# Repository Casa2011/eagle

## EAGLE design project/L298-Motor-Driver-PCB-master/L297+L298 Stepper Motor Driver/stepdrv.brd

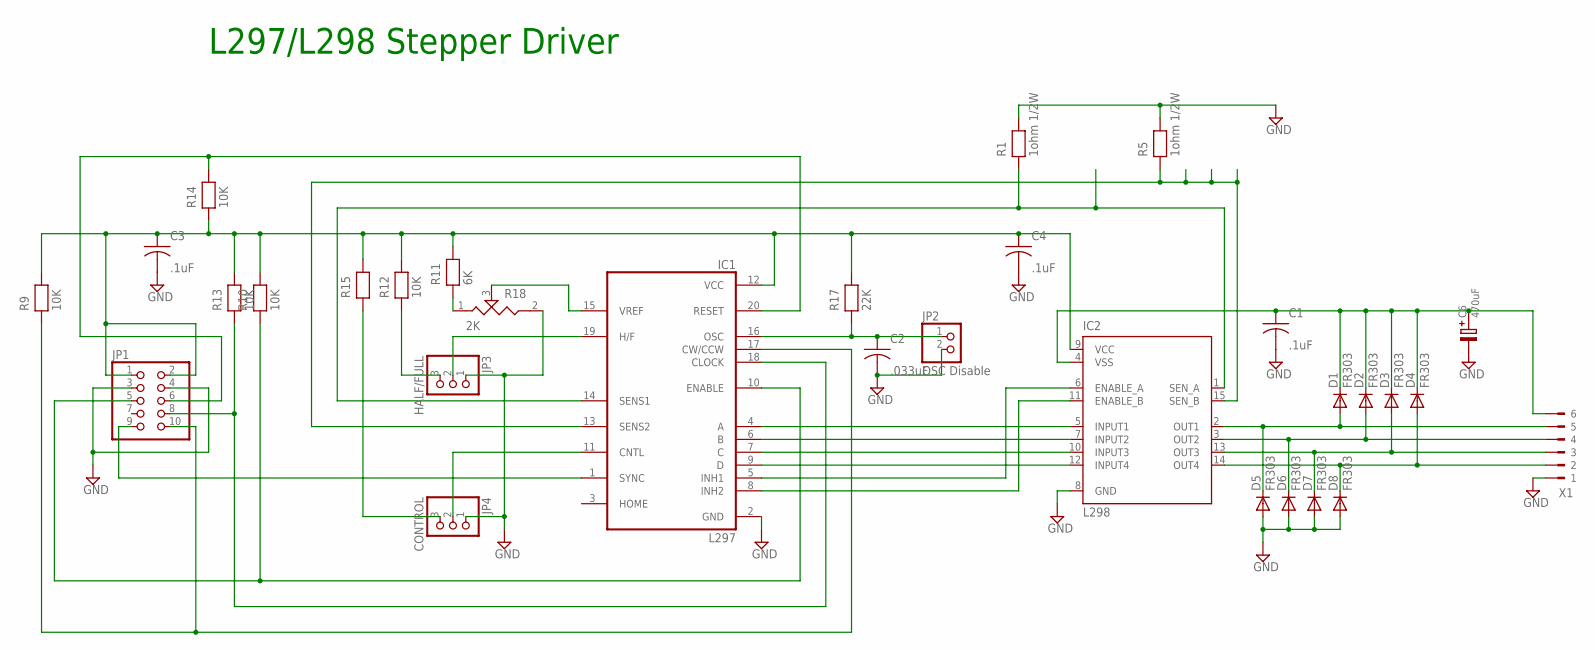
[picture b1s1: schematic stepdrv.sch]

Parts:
C1, C3, C4: .1uF; C-5
C2: .033uF; C-5
C6: 470uF; E5,0-12
D1, D2, D3, D4, D5, D6, D7, D8: FR303; DO201-15
IC1: L297; DIL20
IC2: L298; MULTIWATT-15
JP1: PINHD-2X5; 2X05
JP2: OSC Disable; 1X02
JP3: HALF/FULL; 1X03
JP4: CONTROL; 1X03
R1, R5: 1ohm 1/2W; R-12,5
R9, R10, R12, R13, R14: 10K; R-10
R11: 6K; R-10
R15: RESEU-10; R-10
R17: 22K; R-10
R18: 2K; PT-10S
X1: 90-6

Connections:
GND: C1.2, C2.2, C3.2, C4.2, C6.-, D5.A, D6.A, D7.A, D8.A, IC1.2 (GND), IC2.8 (GND), JP1.3, JP1.4, JP2.2, JP3.1, JP4.1, R1.2, R5.2, R18.2, X1.1
unnamed: D1.A, D5.C, IC2.2 (OUT1), X1.5
unnamed: IC1.4 (A), IC2.5 (INPUT1)
unnamed: IC1.6 (B), IC2.7 (INPUT2)
unnamed: IC1.7 (C), IC2.10 (INPUT3)
unnamed: IC1.9 (D), IC2.12 (INPUT4)
unnamed: IC1.14 (SENS1), IC2.1 (SEN_A), R1.1
unnamed: IC1.13 (SENS2), IC2.15 (SEN_B), R5.1
unnamed: IC1.1 (SYNC), JP1.9
unnamed: IC1.18 (CLOCK), JP1.8, R13.1
unnamed: IC1.17 (CW/CCW), JP1.10, R9.1
unnamed: C2.1, IC1.16 (OSC), JP2.1, R17.1
unnamed: IC1.20 (RESET), JP1.6, R14.2
unnamed: R11.1, R18.1
unnamed: IC1.19 (H/F), JP3.2
unnamed: IC1.11 (CNTL), JP4.2
unnamed: IC1.15 (VREF), R18.3
unnamed: JP3.3, R12.1
unnamed: D2.A, D6.C, IC2.3 (OUT2), X1.4
unnamed: IC1.5 (INH1), IC2.6 (ENABLE_A)
unnamed: IC1.8 (INH2), IC2.11 (ENABLE_B)
unnamed: D3.A, D7.C, IC2.13 (OUT3), X1.3
unnamed: D4.A, D8.C, IC2.14 (OUT4), X1.2
unnamed: IC1.10 (ENABLE), JP1.5, R10.1
unnamed: JP4.3, R15.1
VCC: C3.1, C4.1, IC1.12 (VCC), IC2.9 (VCC), JP1.1, JP1.2, R9.2, R10.2, R11.2, R12.2, R13.2, R14.1, R15.2, R17.2
VSS: C1.1, C6.+, D1.C, D2.C, D3.C, D4.C, IC2.4 (VSS), X1.6

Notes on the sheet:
L297/L298 Stepper Driver

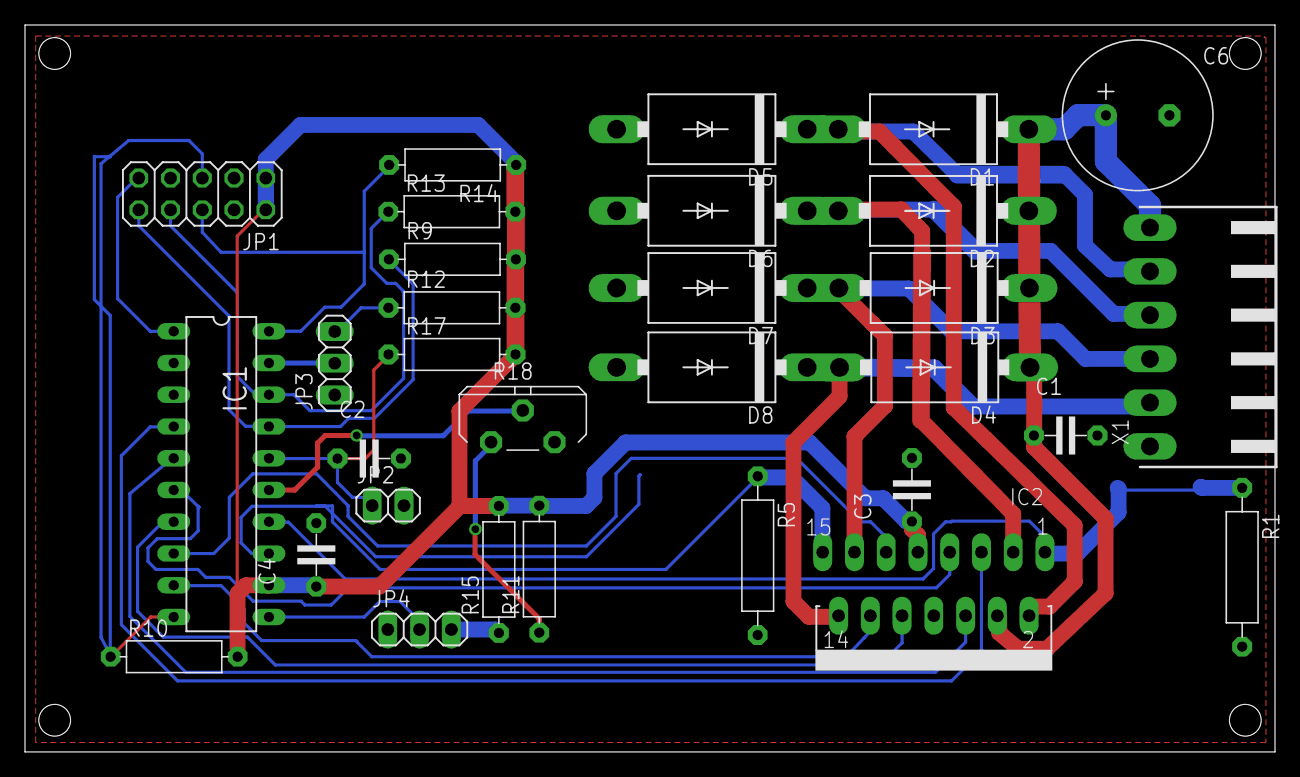
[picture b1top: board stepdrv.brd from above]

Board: 2 copper layers, 100.0 x 58.2 mm, 31 parts (0 on the bottom side), 27 nets.

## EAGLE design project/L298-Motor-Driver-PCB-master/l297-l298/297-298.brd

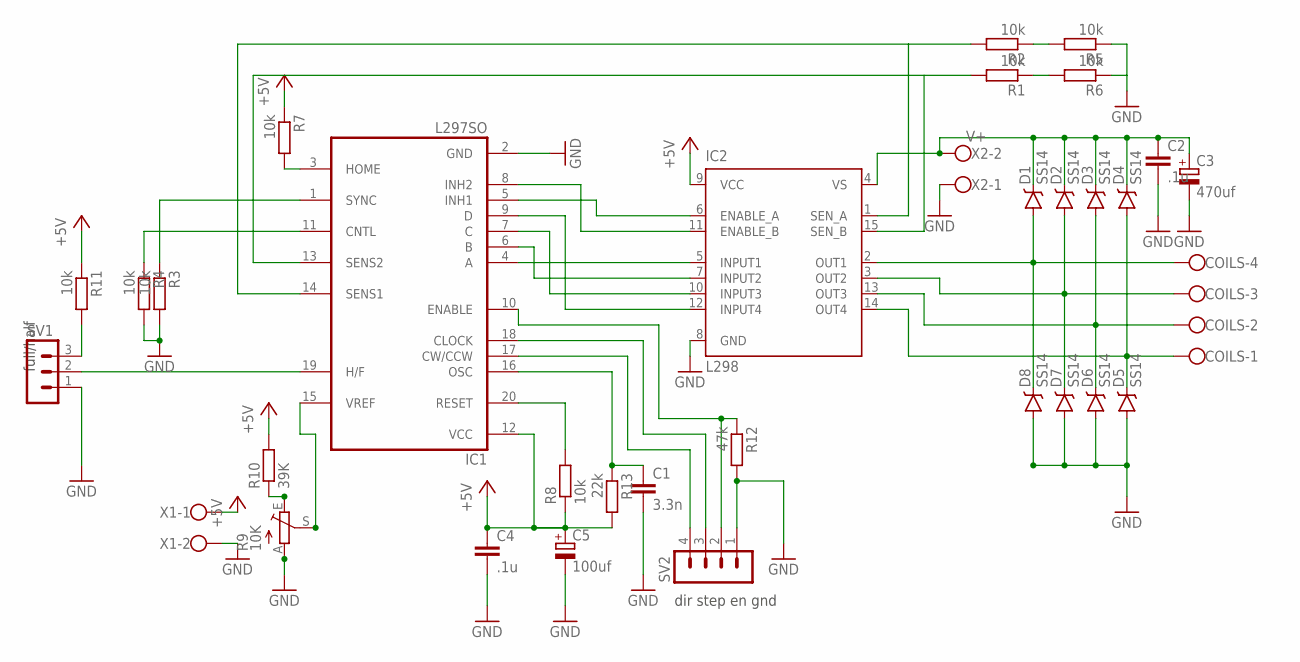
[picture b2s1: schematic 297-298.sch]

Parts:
C1: 3.3n; C0805
C2, C4: .1u; C0805
C3: 470uf; E3,5-8
C5: 100uf; E3,5-8
COILS: W237-4
D1, D2, D3, D4, D5, D6, D7, D8: SS14; SMA-DIODE
IC1: L297SO; SO20
IC2: L298; MULTIWATT-15
R1, R2, R5, R6: 10k; R2512
R3, R4, R7, R8, R11: 10k; R0805
R9: 10K; CA9V
R10: 39K; R0805
R12: 47k; R0805
R13: 22k; R0805
SV1: MA03-1
SV2: MA04-1
X1: W237-102
X2: V+; W237-102

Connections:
+5V: C4.1, C5.+, IC1.12 (VCC), IC2.9 (VCC), R7.1, R8.1, R10.2, R11.1, R13.2, X1.1
GND: C1.2, C2.2, C3.-, C4.2, C5.-, D5.A, D6.A, D7.A, D8.A, IC1.2 (GND), IC2.8 (GND), R3.2, R4.2, R5.P$1 (1), R6.P$1 (1), R9.A, R12.2, SV1.1, SV2.1, X1.2, X2.1
unnamed: IC1.4 (A), IC2.5 (INPUT1)
unnamed: IC1.6 (B), IC2.7 (INPUT2)
unnamed: IC1.7 (C), IC2.10 (INPUT3)
unnamed: IC1.9 (D), IC2.12 (INPUT4)
unnamed: IC1.8 (INH2), IC2.11 (ENABLE_B)
unnamed: IC1.5 (INH1), IC2.6 (ENABLE_A)
unnamed: IC1.15 (VREF), R9.S
unnamed: R9.E, R10.1
unnamed: COILS.4, D1.A, D8.C, IC2.2 (OUT1)
unnamed: COILS.3, D2.A, D7.C, IC2.3 (OUT2)
unnamed: COILS.2, D3.A, D6.C, IC2.13 (OUT3)
unnamed: COILS.1, D4.A, D5.C, IC2.14 (OUT4)
unnamed: IC1.13 (SENS2), IC2.15 (SEN_B), R1.P$2 (2)
unnamed: IC1.14 (SENS1), IC2.1 (SEN_A), R2.P$2 (2)
unnamed: IC1.1 (SYNC), R3.1
unnamed: IC1.19 (H/F), SV1.2
unnamed: R11.2, SV1.3
unnamed: IC1.10 (ENABLE), R12.1, SV2.2
unnamed: IC1.18 (CLOCK), SV2.3
unnamed: IC1.17 (CW/CCW), SV2.4
unnamed: C1.1, IC1.16 (OSC), R13.1
unnamed: IC1.11 (CNTL), R4.1
unnamed: IC1.3 (HOME), R7.2
unnamed: C2.1, C3.+, D1.C, D2.C, D3.C, D4.C, IC2.4 (VS), X2.2
unnamed: IC1.20 (RESET), R8.2
unnamed: R2.P$1 (1), R5.P$2 (2)
unnamed: R1.P$1 (1), R6.P$2 (2)

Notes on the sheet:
dir step en gnd
full/half

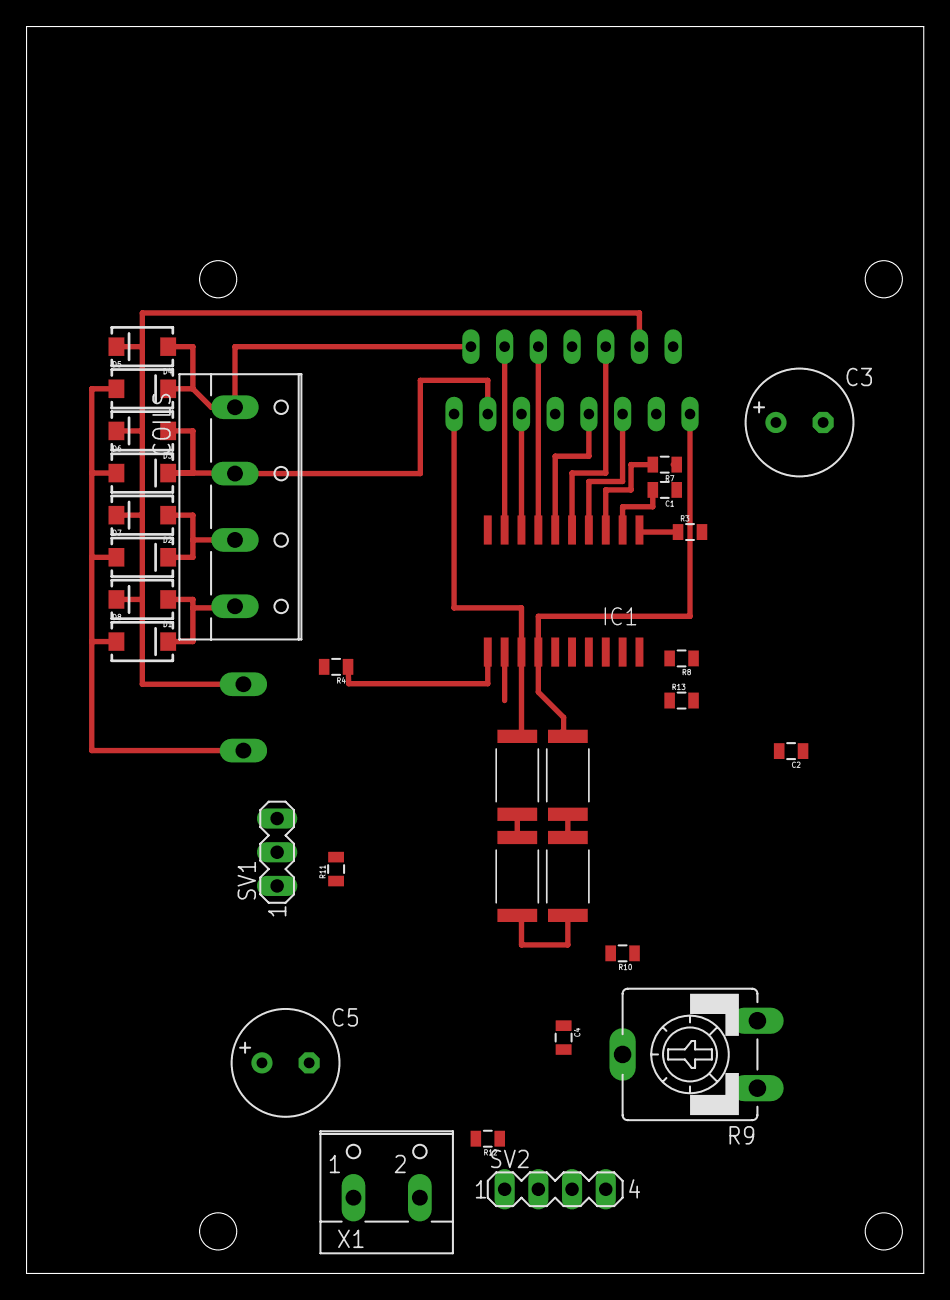
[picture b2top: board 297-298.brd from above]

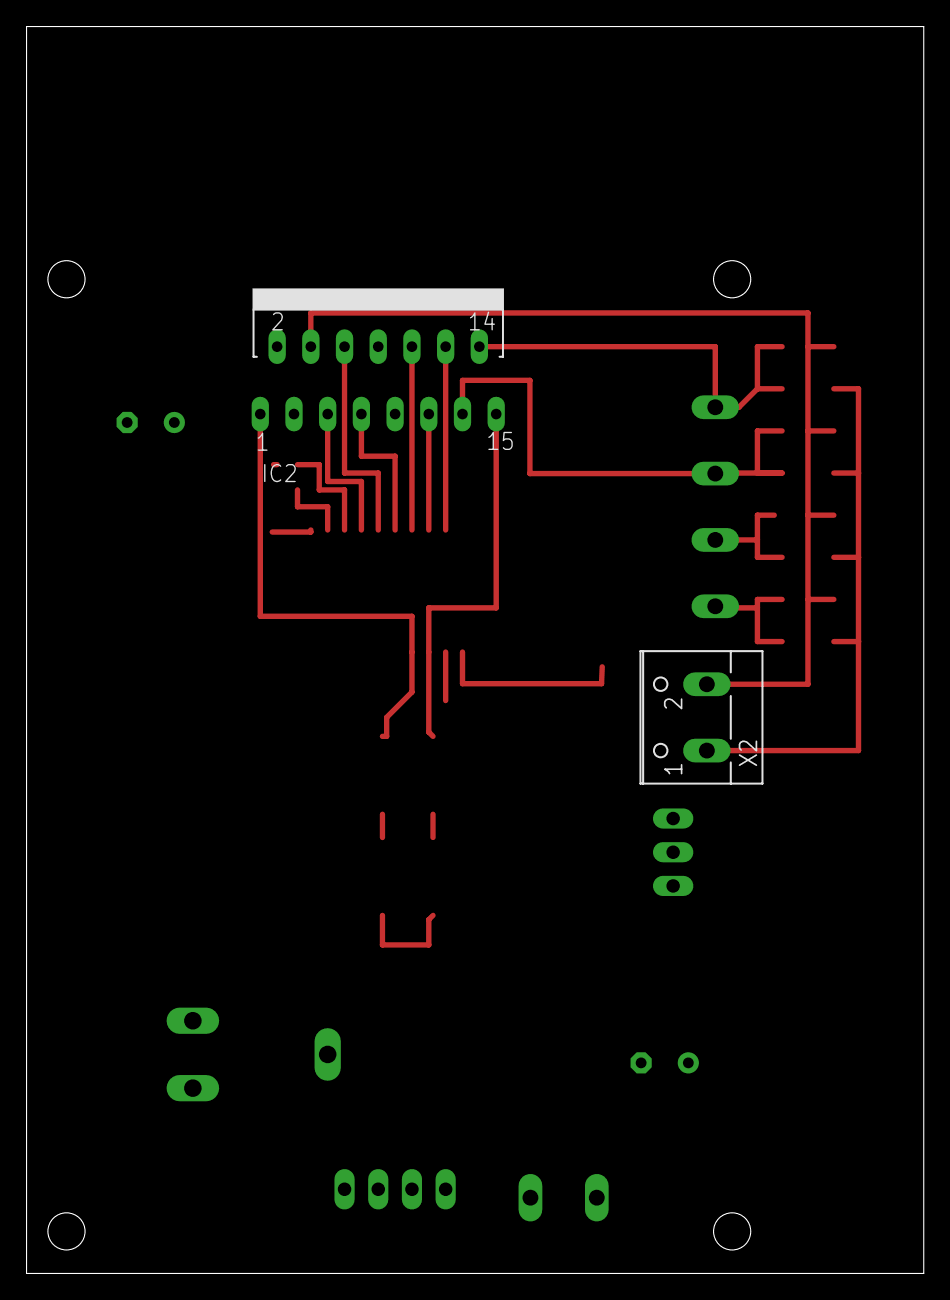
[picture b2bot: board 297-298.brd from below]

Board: 2 copper layers, 67.6 x 94.0 mm, 33 parts (2 on the bottom side), 29 nets.

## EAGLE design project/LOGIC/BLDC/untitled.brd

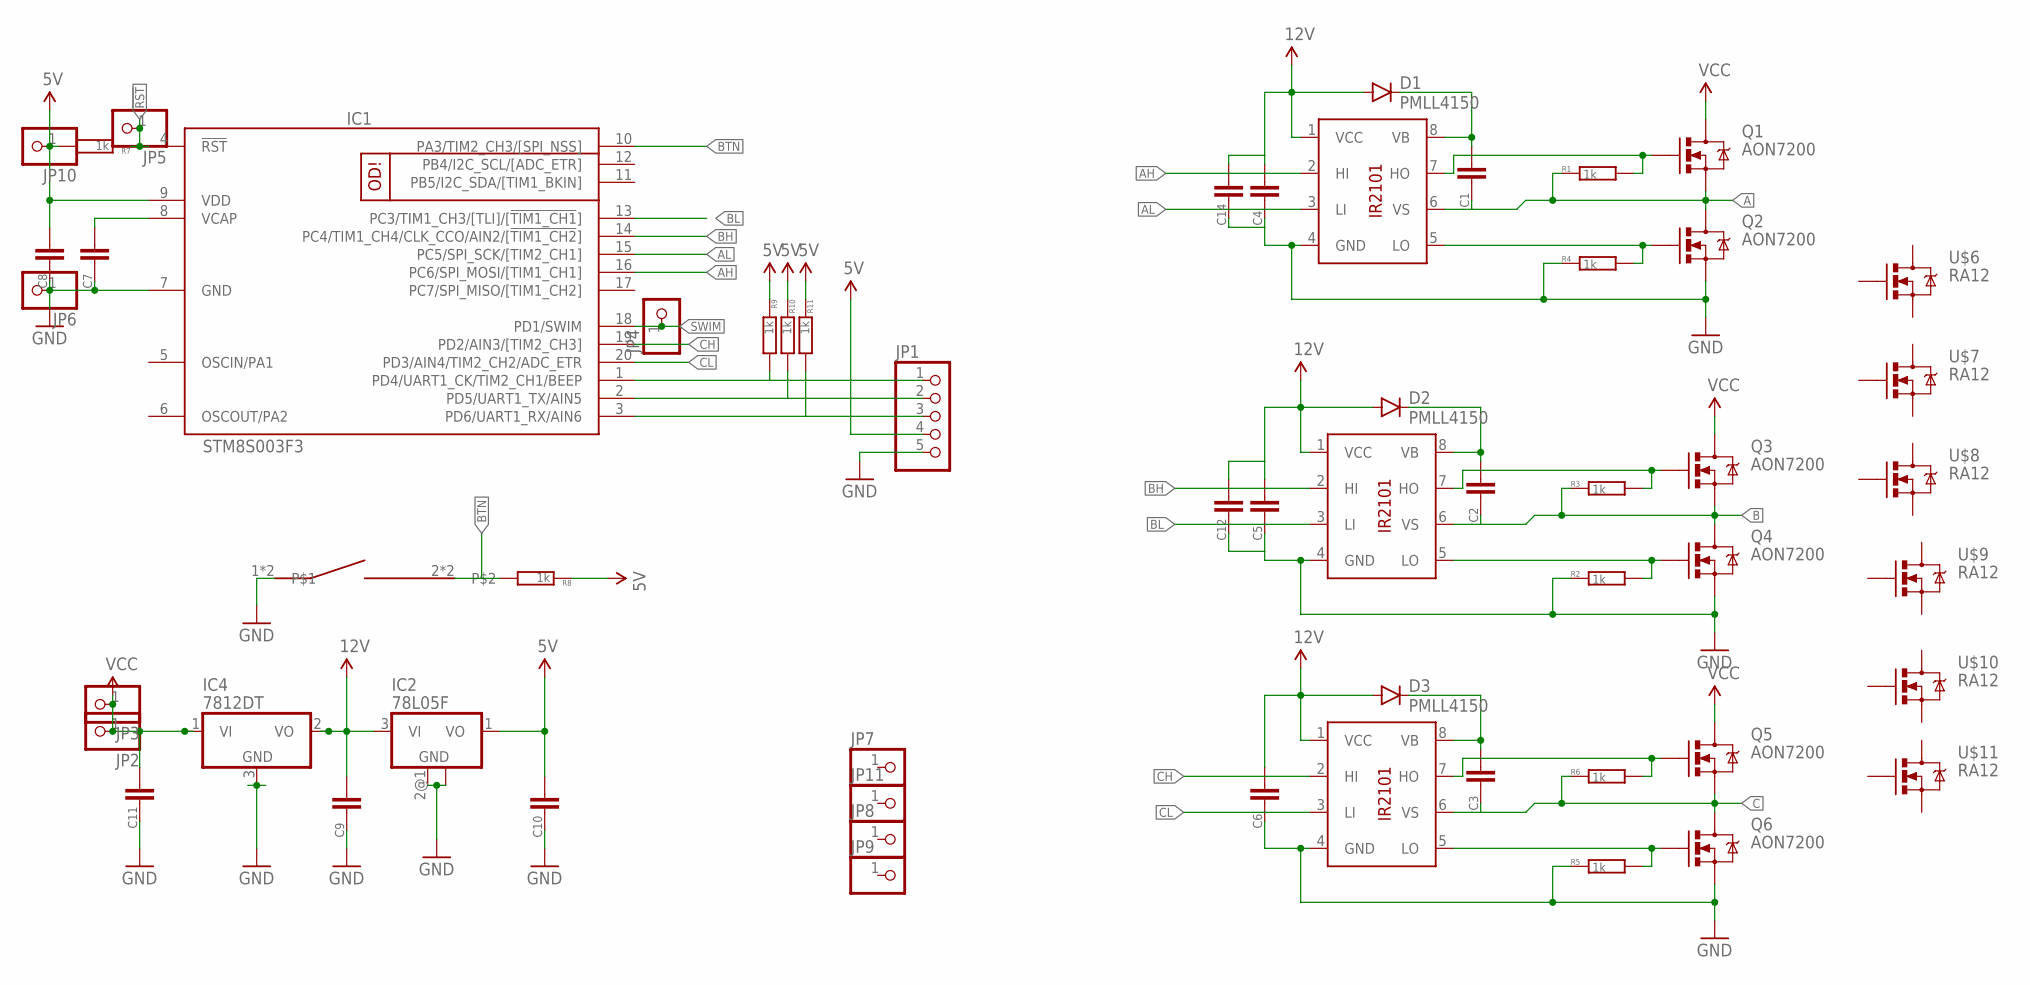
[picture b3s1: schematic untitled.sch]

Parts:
C1, C2, C3, C4, C5, C6, C8, C9, C10, C11, C12, C14: CC0805; C0805
C7: CC0603; C0603
D1, D2, D3: PMLL4150; SOD80C
IC1: STM8S003F3; TSSOP20
IC2: 78L05F; SOT89
IC4: 7812DT; TO252
JP1: PINHD-1X05_2.00; 1X05M
JP2, JP3, JP4, JP5, JP6, JP10: PINHD-1X1; 1X01
JP7, JP8, JP9, JP11: PINHD-1X01_2.54-90°; 1X01/90
Q1, Q2, Q3, Q4, Q5, Q6: AON7200; DFN3X3
R1, R2, R3, R4, R5, R6, R7, R8, R9, R10, R11: 1k; 0603
U$1, U$2, U$4: IR2101; SO08
U$5: BUTTON1
U$6, U$7, U$8, U$9, U$10, U$11: RA12; POWERPAK_SO8

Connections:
5V: C8.1, C10.1, IC1.9 (VDD), IC2.1 (VO), JP1.4, JP10.1, R7.2, R8.1, R9.1, R10.1, R11.1
12V: C4.1, C5.1, C6.1, C9.1, C12.1, C14.1, D1.A, D2.A, D3.A, IC2.3 (VI), IC4.2 (VO), U$1.1 (VCC), U$2.1 (VCC), U$4.1 (VCC)
!RST: IC1.4 (!RST), JP5.1, R7.1
A: C1.2, Q1.S:1 (S), Q1.S:2 (S), Q1.S:3 (S), Q2.D, Q2.D:1 (D), Q2.D:2 (D), Q2.D:3 (D), Q2.D:4 (D), Q2.D:5 (D), Q2.D:6 (D), R1.1, U$1.6 (VS)
AH: IC1.16 (PC6/SPI_MOSI/[TIM1_CH1]), U$1.2 (HI)
AL: IC1.15 (PC5/SPI_SCK/[TIM2_CH1]), U$1.3 (LI)
B: C2.2, Q3.S:1 (S), Q3.S:2 (S), Q3.S:3 (S), Q4.D, Q4.D:1 (D), Q4.D:2 (D), Q4.D:3 (D), Q4.D:4 (D), Q4.D:5 (D), Q4.D:6 (D), R3.1, U$2.6 (VS)
BH: IC1.14 (PC4/TIM1_CH4/CLK_CCO/AIN2/[!TIM1_CH2!]), U$2.2 (HI)
BL: IC1.13 (PC3/TIM1_CH3/[TLI]/[!TIM1_CH1!]), U$2.3 (LI)
BTN: IC1.10 (PA3/TIM2_CH3/[SPI_NSS]), R8.2, U$5.2, U$5.4
C: C3.2, Q5.S:1 (S), Q5.S:2 (S), Q5.S:3 (S), Q6.D, Q6.D:1 (D), Q6.D:2 (D), Q6.D:3 (D), Q6.D:4 (D), Q6.D:5 (D), Q6.D:6 (D), R6.1, U$4.6 (VS)
CH: IC1.19 (PD2/AIN3/[TIM2_CH3]), U$4.2 (HI)
CL: IC1.20 (PD3/AIN4/TIM2_CH2/ADC_ETR), U$4.3 (LI)
GND: C4.2, C5.2, C6.2, C7.2, C8.2, C9.2, C10.2, C11.2, C12.2, C14.2, IC1.7 (GND), IC2.2 (GND), IC2.2@1 (GND), IC4.3 (GND), JP1.5, JP6.1, Q2.S:1 (S), Q2.S:2 (S), Q2.S:3 (S), Q4.S:1 (S), Q4.S:2 (S), Q4.S:3 (S), Q6.S:1 (S), Q6.S:2 (S), Q6.S:3 (S), R2.1, R4.1, R5.1, U$1.4 (GND), U$2.4 (GND), U$4.4 (GND), U$5.1, U$5.3
unnamed: Q3.G, R3.2, U$2.7 (HO)
unnamed: C2.1, D2.C, U$2.8 (VB)
unnamed: Q4.G, R2.2, U$2.5 (LO)
unnamed: Q1.G, R1.2, U$1.7 (HO)
unnamed: C1.1, D1.C, U$1.8 (VB)
unnamed: Q5.G, R6.2, U$4.7 (HO)
unnamed: Q2.G, R4.2, U$1.5 (LO)
unnamed: C3.1, D3.C, U$4.8 (VB)
unnamed: Q6.G, R5.2, U$4.5 (LO)
unnamed: IC1.1 (PD4/UART1_CK/TIM2_CH1/BEEP), JP1.1, R9.2
unnamed: IC1.2 (PD5/UART1_TX/AIN5), JP1.2, R10.2
unnamed: IC1.3 (PD6/UART1_RX/AIN6), JP1.3, R11.2
unnamed: C7.1, IC1.8 (VCAP)
SWIM: IC1.18 (PD1/SWIM), JP4.1
VCC: C11.1, IC4.1 (VI), JP2.1, JP3.1, Q1.D, Q1.D:1 (D), Q1.D:2 (D), Q1.D:3 (D), Q1.D:4 (D), Q1.D:5 (D), Q1.D:6 (D), Q3.D, Q3.D:1 (D), Q3.D:2 (D), Q3.D:3 (D), Q3.D:4 (D), Q3.D:5 (D), Q3.D:6 (D), Q5.D, Q5.D:1 (D), Q5.D:2 (D), Q5.D:3 (D), Q5.D:4 (D), Q5.D:5 (D), Q5.D:6 (D)

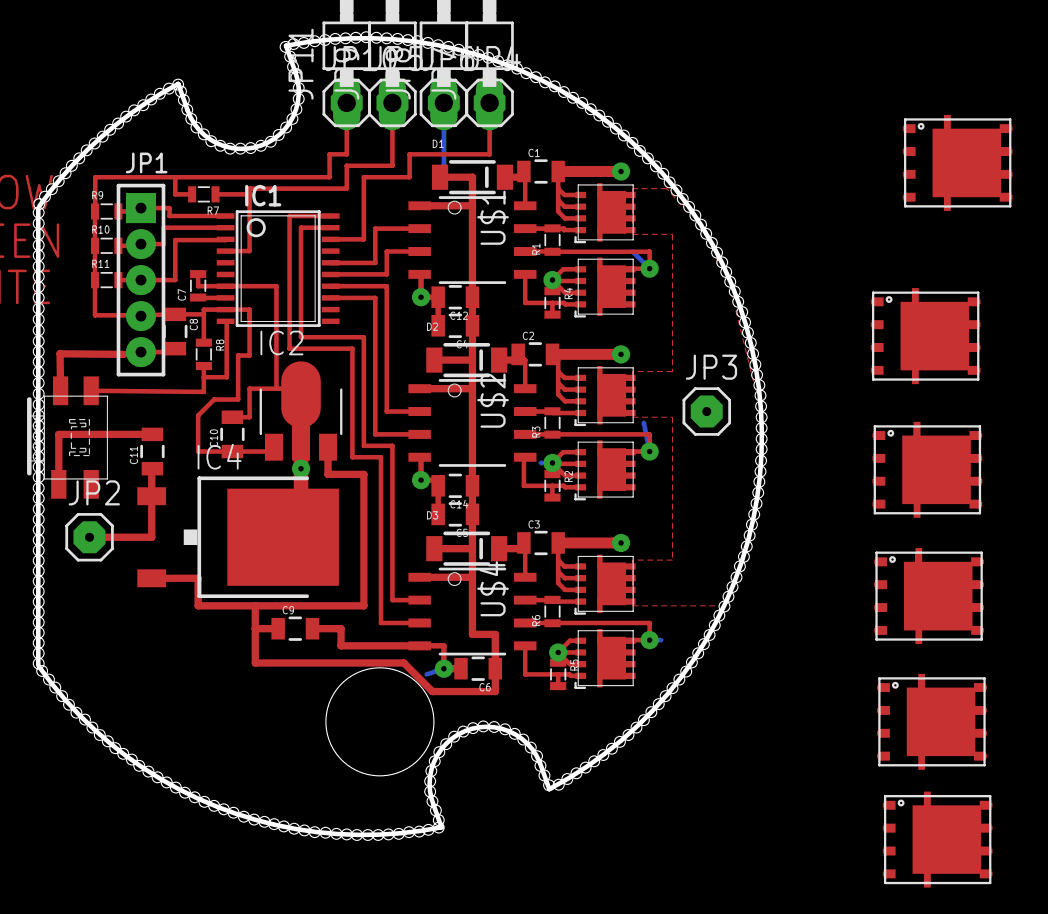
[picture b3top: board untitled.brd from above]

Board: 2 copper layers, 40.2 x 44.3 mm, 58 parts (0 on the bottom side), 29 nets.

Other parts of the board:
U$3: AOKT-1

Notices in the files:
parts and their libraries:
SparkFun-Aesthetics: Licensing: Creative Commons ShareAlike 4.0 International - https://creativecommons.org/licenses/by-sa/4.0
